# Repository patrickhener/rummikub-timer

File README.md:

# Rummikub Timer

This project is a Rummikub timer. It has the following functions:

- Set a countdown time (default: 1 minute)
- Start timer by pressing big button
- Reset and start timer by pressing it again
- Blink big button when reaching 10 second time zone
- Alarm if time is up
- Nice laser-cut enclosure
- Runs on battery
- Chargable via USB-C
- Incorporates a display

## Hardware

The project consists of the following components:

- Arduino Nano
- LiPo Battery
- TP4056 USB-C charging 
- Different push buttons (28mm, 100mm with LED)
- On/Off Switch
- Active Buzzer
- MT3608 Step-Up Converter
- 0,96" OLED Display
- Small components like resistors and a mosfet

## Images

## Lessons learned

The box is really tight, so I had to improvise and cut away from some of the buttons. Also The top button is not fixed into casing as it is to tight. But that in fact is better, so you can assamble and then maintaine it, by just pulling the big button out. As the button will be pushed it is not a problem it is not fixed anyways.

## Hazard warning

If you build it like I did never run and charge at the same time. The missing safe charge circuit during load is not sharing the load, so the battery will be over-charged and might caught on fire. I DO NOT HOLD ACCOUNTABILITY FOR DAMAGE TO YOU OR YOUR SURROUNDINGS.

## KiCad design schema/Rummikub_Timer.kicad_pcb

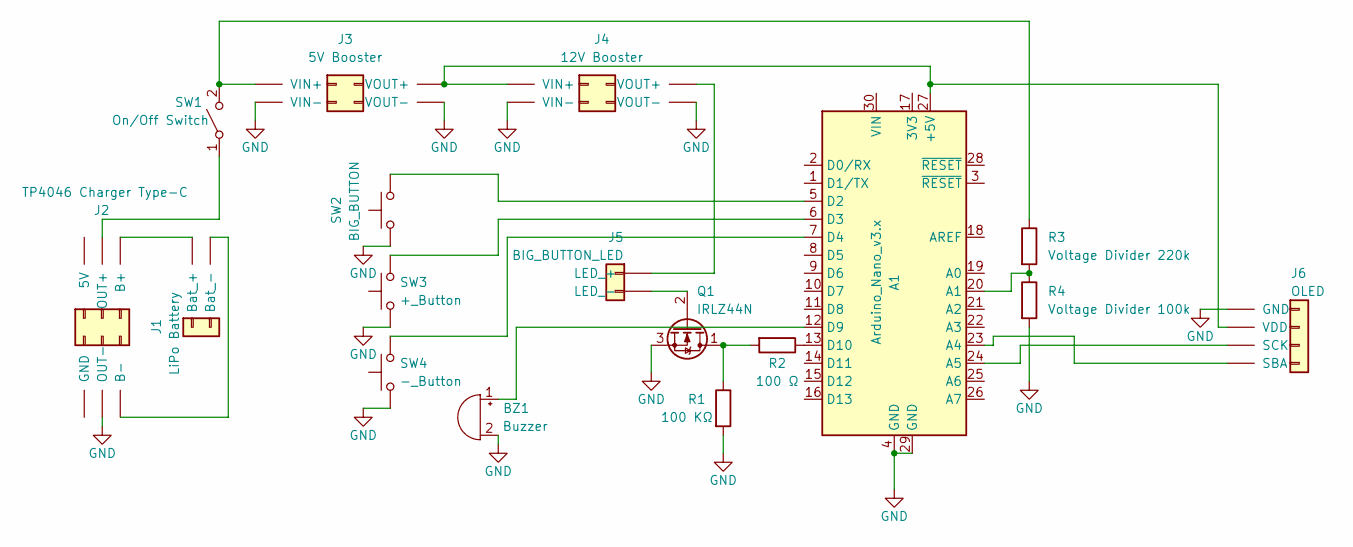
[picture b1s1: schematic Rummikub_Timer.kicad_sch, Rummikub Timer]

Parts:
A1: Arduino_Nano_v3.x; Arduino_Nano
BZ1: Buzzer; PinHeader_1x02_P2.54mm_Vertical
J1: LiPo Battery; PinHeader_1x02_P2.54mm_Vertical
J2: TP4046 Charger Type-C; TP4056-18650
J3: 5V Booster; MT3608_module
J4: 12V Booster; MT3608_module
J5: BIG_BUTTON_LED; PinHeader_1x02_P2.54mm_Vertical
J6: OLED; PinHeader_1x04_P2.54mm_Vertical
Q1: IRLZ44N; TO-220-3_Vertical
R1: 100 KΩ; R_Axial_DIN0207_L6.3mm_D2.5mm_P7.62mm_Horizontal
R2: 100 Ω; R_Axial_DIN0207_L6.3mm_D2.5mm_P7.62mm_Horizontal
R3: Voltage Divider 220k; R_Axial_DIN0207_L6.3mm_D2.5mm_P7.62mm_Horizontal
R4: Voltage Divider 100k; R_Axial_DIN0207_L6.3mm_D2.5mm_P7.62mm_Horizontal
SW1: On/Off Switch; PinHeader_1x02_P2.54mm_Vertical
SW2: BIG_BUTTON; PinHeader_1x02_P2.54mm_Vertical
SW3: +_Button; PinHeader_1x02_P2.54mm_Vertical
SW4: -_Button; PinHeader_1x02_P2.54mm_Vertical

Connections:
GND: A1.4 (GND), A1.29 (GND), BZ1.2 (+), J2.4 (OUT-), J3.2 (VIN-), J3.4 (VOUT-), J4.2 (VIN-), J4.4 (VOUT-), J6.1 (GND), Q1.3 (S), R1.2, R4.2, SW2.1, SW3.1, SW4.1
unnamed: A1.5 (D2), SW2.2
unnamed: A1.6 (D3), SW3.2
unnamed: A1.7 (D4), SW4.2
unnamed: A1.12 (D9), BZ1.1 (-)
unnamed: A1.13 (D10), R2.1
unnamed: A1.20 (A1), R3.2, R4.1
unnamed: A1.23 (A4), J6.4 (SBA)
unnamed: A1.24 (A5), J6.3 (SCK)
unnamed: A1.27 (+5V), J3.3 (VOUT+), J4.1 (VIN+), J6.2 (VDD)
unnamed: J1.1 (Bat_+), J2.5 (B+)
unnamed: J1.2 (Bat_-), J2.6 (B-)
unnamed: J2.3 (OUT+), SW1.1 (A)
unnamed: J3.1 (VIN+), R3.1, SW1.2 (B)
unnamed: J4.3 (VOUT+), J5.1 (LED_+)
unnamed: J5.2 (LED_-), Q1.2 (G)
unnamed: Q1.1 (D), R1.1, R2.2

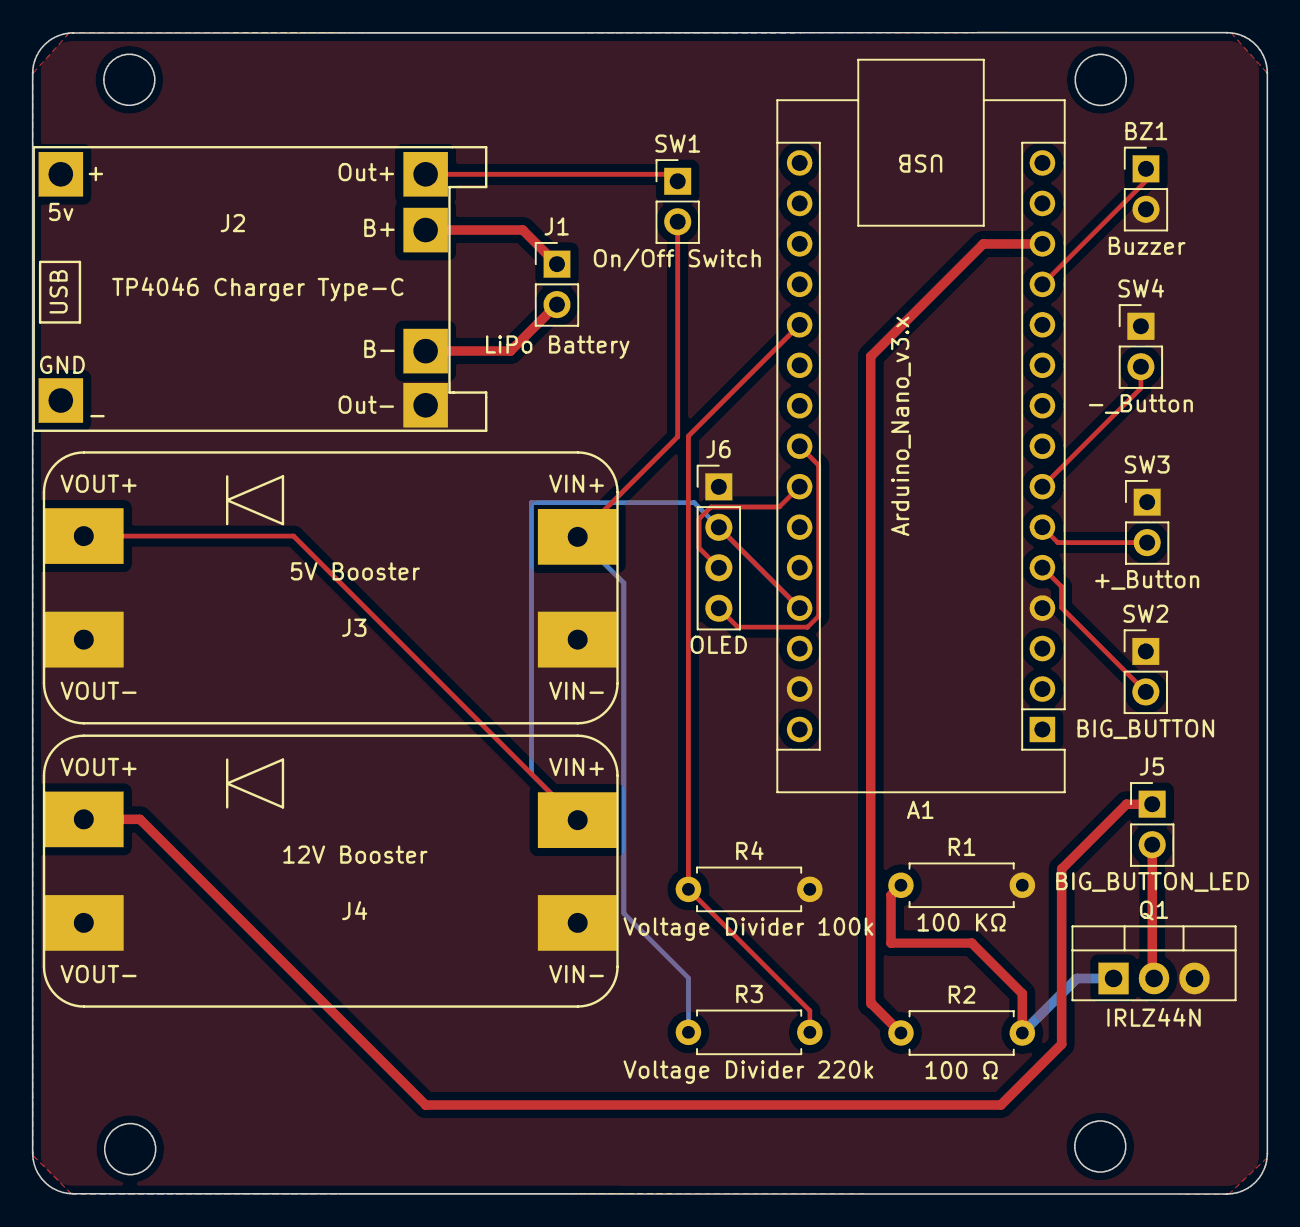
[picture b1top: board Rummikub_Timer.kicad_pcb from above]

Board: 2 copper layers, 77.5 x 72.9 mm, 17 parts (0 on the bottom side), 17 nets.
